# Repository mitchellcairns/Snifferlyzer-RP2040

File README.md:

# Snifferlyzer PCB
Snifferlyzer is a PCB for RP2040 facilitating the device to be used as a logic analyzer/USB Sniffer.

## Software and PCB License
<br />This firmware and PCB model are licensed under a <a rel="license" href="http://creativecommons.org/licenses/by-nc-sa/3.0/">Creative Commons Attribution-NonCommercial-ShareAlike 3.0 Unported License</a>.

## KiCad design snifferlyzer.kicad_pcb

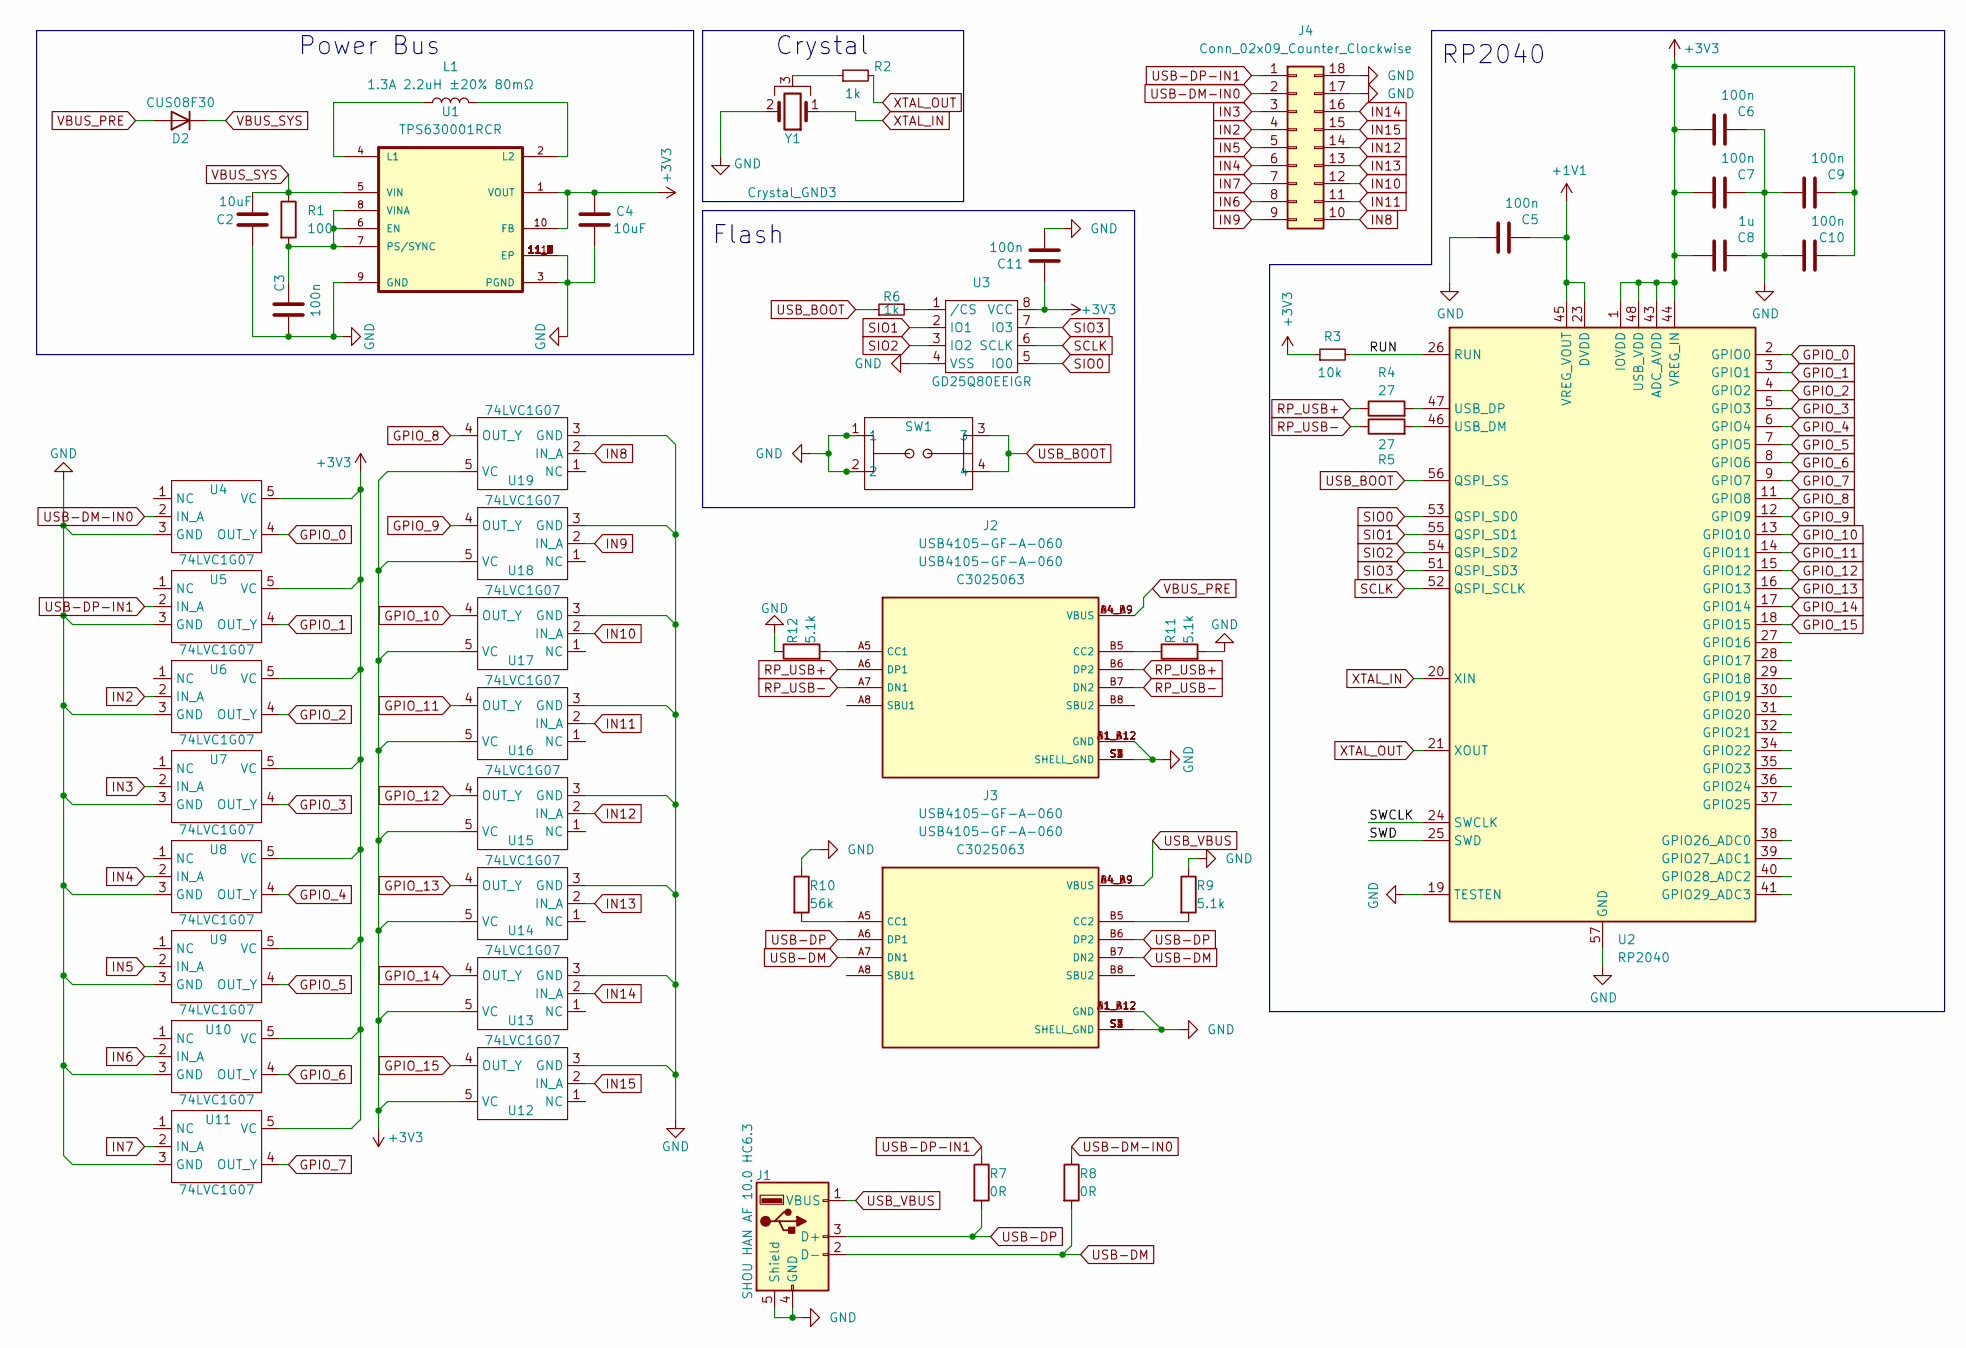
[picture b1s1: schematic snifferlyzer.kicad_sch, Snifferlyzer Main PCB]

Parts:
C2, C4: 10uF; C_0805_2012Metric
C3, C6, C11: 100n; C_0201_0603Metric
C5, C7, C9, C10: 100n; C_0402_1005Metric
C8: 1u; C_0402_1005Metric
D2: CUS08F30; D_SOD-323_HandSoldering; MPN CUS08F30
J1: SHOU HAN AF 10.0 HC6.3; AF 10.0 HC6.3; MPN AF 10.0 HC6.3; LCSC C456017
J2, J3: USB4105-GF-A-060; GCT_USB4105-GF-A-060; MPN USB4105-GF-A-060
J4: Conn_02x09_Counter_Clockwise; PinHeader_2x09_P2.54mm_Vertical; MPN X6521WV-2x09H-C60D30; LCSC C706899
L1: 1.3A 2.2uH ±20% 80mΩ; L_1008_2520Metric; MPN MIP25202R2MBE; LCSC C315721
R1: 100; R_0201_0603Metric
R2, R6: 1k; R_0201_0603Metric
R3: 10k; R_0201_0603Metric
R4, R5: 27; R_0201_0603Metric
R7, R8: 0R; R_0805_2012Metric
R9, R11, R12: 5.1k; R_0805_2012Metric
R10: 56k; R_0805_2012Metric
SW1: 1TS026A-1000-0550; MPN 1TS026A-1000-0550; LCSC C913778
U1: TPS630001RCR; VREG_V62_16624-01YE; MPN TPS63001DRCR
U2: RP2040; QFN-56-1EP_7x7mm_P0.4mm_EP3.2x3.2mm; MPN RP2040
U3: GD25Q80EEIGR; USON-8-EP(2x3); MPN GD25Q80EEIGR; LCSC C2874937
U4, U5, U6, U7, U8, U9, U10, U11, U12, U13, U14, U15, U16, U17, U18, U19: 74LVC1G07; SOT-353_SC-70-5; MPN SN74LVC1G07DCKR(UMW); LCSC C7394033
Y1: Crystal_GND3; Resonator_SMD_Murata_CSTxExxV-3Pin_3.0x1.1mm; MPN CSTNE12M0GH5L000R0

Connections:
+1V1: C5.2, U2.23 (DVDD), U2.45 (VREG_VOUT), U2.50 (DVDD)
+3V3: C4.1, C6.1, C7.1, C8.1, C9.2, C10.2, C11.1, R3.1, U1.1 (VOUT), U1.10 (FB), U2.1 (IOVDD), U2.10 (IOVDD), U2.22 (IOVDD), U2.33 (IOVDD), U2.42 (IOVDD), U2.43 (ADC_AVDD), U2.44 (VREG_IN), U2.48 (USB_VDD), U2.49 (IOVDD), U3.8 (VCC), U4.5 (VC), U5.5 (VC), U6.5 (VC), U7.5 (VC), U8.5 (VC), U9.5 (VC), U10.5 (VC), U11.5 (VC), U12.5 (VC), U13.5 (VC), U14.5 (VC), U15.5 (VC), U16.5 (VC), U17.5 (VC), U18.5 (VC), U19.5 (VC)
/RUN: R3.2, U2.26 (RUN)
/SWCLK: U2.24 (SWCLK)
/SWD: U2.25 (SWD)
GND: C2.1, C3.1, C4.2, C5.1, C6.2, C7.2, C8.2, C9.1, C10.1, C11.2, J1.4 (GND), J1.5 (Shield), J2.A1_B12 (GND), J2.B1_A12 (GND), J2.S1 (SHELL_GND), J2.S2 (SHELL_GND), J2.S3 (SHELL_GND), J2.S4 (SHELL_GND), J3.A1_B12 (GND), J3.B1_A12 (GND), J3.S1 (SHELL_GND), J3.S2 (SHELL_GND), J3.S3 (SHELL_GND), J3.S4 (SHELL_GND), J4.17, J4.18, R9.1, R10.1, R11.2, R12.1, SW1.1, SW1.2, U1.3 (PGND), U1.9 (GND), U1.11 (EP), U1.11_1 (EP), U1.11_2 (EP), U1.11_3 (EP), U1.11_4 (EP), U1.11_5 (EP), U1.11_6 (EP), U1.11_7 (EP), U1.11_8 (EP), U2.19 (TESTEN), U2.57 (GND), U3.4 (VSS), U4.3 (GND), U5.3 (GND), U6.3 (GND), U7.3 (GND), U8.3 (GND), U9.3 (GND), U10.3 (GND), U11.3 (GND), U12.3 (GND), U13.3 (GND), U14.3 (GND), U15.3 (GND), U16.3 (GND), U17.3 (GND), U18.3 (GND), U19.3 (GND), Y1.2
GPIO_0: U2.2 (GPIO0), U4.4 (OUT_Y)
GPIO_1: U2.3 (GPIO1), U5.4 (OUT_Y)
GPIO_2: U2.4 (GPIO2), U6.4 (OUT_Y)
GPIO_3: U2.5 (GPIO3), U7.4 (OUT_Y)
GPIO_4: U2.6 (GPIO4), U8.4 (OUT_Y)
GPIO_5: U2.7 (GPIO5), U9.4 (OUT_Y)
GPIO_6: U2.8 (GPIO6), U10.4 (OUT_Y)
GPIO_7: U2.9 (GPIO7), U11.4 (OUT_Y)
GPIO_8: U2.11 (GPIO8), U19.4 (OUT_Y)
GPIO_9: U2.12 (GPIO9), U18.4 (OUT_Y)
GPIO_10: U2.13 (GPIO10), U17.4 (OUT_Y)
GPIO_11: U2.14 (GPIO11), U16.4 (OUT_Y)
GPIO_12: U2.15 (GPIO12), U15.4 (OUT_Y)
GPIO_13: U2.16 (GPIO13), U14.4 (OUT_Y)
GPIO_14: U2.17 (GPIO14), U13.4 (OUT_Y)
GPIO_15: U2.18 (GPIO15), U12.4 (OUT_Y)
IN2: J4.4, U6.2 (IN_A)
IN3: J4.3, U7.2 (IN_A)
IN4: J4.6, U8.2 (IN_A)
IN5: J4.5, U9.2 (IN_A)
IN6: J4.8, U10.2 (IN_A)
IN7: J4.7, U11.2 (IN_A)
IN8: J4.10, U19.2 (IN_A)
IN9: J4.9, U18.2 (IN_A)
IN10: J4.12, U17.2 (IN_A)
IN11: J4.11, U16.2 (IN_A)
IN12: J4.14, U15.2 (IN_A)
IN13: J4.13, U14.2 (IN_A)
IN14: J4.16, U13.2 (IN_A)
IN15: J4.15, U12.2 (IN_A)
unnamed: J2.A5 (CC1), R12.2
unnamed: J2.B5 (CC2), R11.1
unnamed: J3.A5 (CC1), R10.2
unnamed: J3.B5 (CC2), R9.2
unnamed: R2.1, Y1.3
unnamed: C3.2, R1.2, U1.6 (EN), U1.7 (PS/SYNC), U1.8 (VINA)
unnamed: L1.1, U1.4 (L1)
unnamed: L1.2, U1.2 (L2)
unnamed: R5.2, U2.46 (USB_DM)
unnamed: R4.2, U2.47 (USB_DP)
unnamed: R6.2, U3.1 (/CS)
RP_USB+: J2.A6 (DP1), J2.B6 (DP2), R4.1
RP_USB-: J2.A7 (DN1), J2.B7 (DN2), R5.1
SCLK: U2.52 (QSPI_SCLK), U3.6 (SCLK)
SIO0: U2.53 (QSPI_SD0), U3.5 (IO0)
SIO1: U2.55 (QSPI_SD1), U3.2 (IO1)
SIO2: U2.54 (QSPI_SD2), U3.3 (IO2)
SIO3: U2.51 (QSPI_SD3), U3.7 (IO3)
USB-DM: J1.2 (D-), J3.A7 (DN1), J3.B7 (DN2), R8.2
USB-DM-IN0: J4.2, R8.1, U4.2 (IN_A)
USB-DP: J1.3 (D+), J3.A6 (DP1), J3.B6 (DP2), R7.2
USB-DP-IN1: J4.1, R7.1, U5.2 (IN_A)
USB_BOOT: R6.1, SW1.3, SW1.4, U2.56 (QSPI_SS)
USB_VBUS: J1.1 (VBUS), J3.A4_B9 (VBUS), J3.B4_A9 (VBUS)
VBUS_PRE: D2.2 (A), J2.A4_B9 (VBUS), J2.B4_A9 (VBUS)
VBUS_SYS: C2.2, D2.1 (K), R1.1, U1.5 (VIN)
XTAL_IN: U2.20 (XIN), Y1.1
XTAL_OUT: R2.2, U2.21 (XOUT)

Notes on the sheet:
RP2040
Flash
Crystal
Power Bus

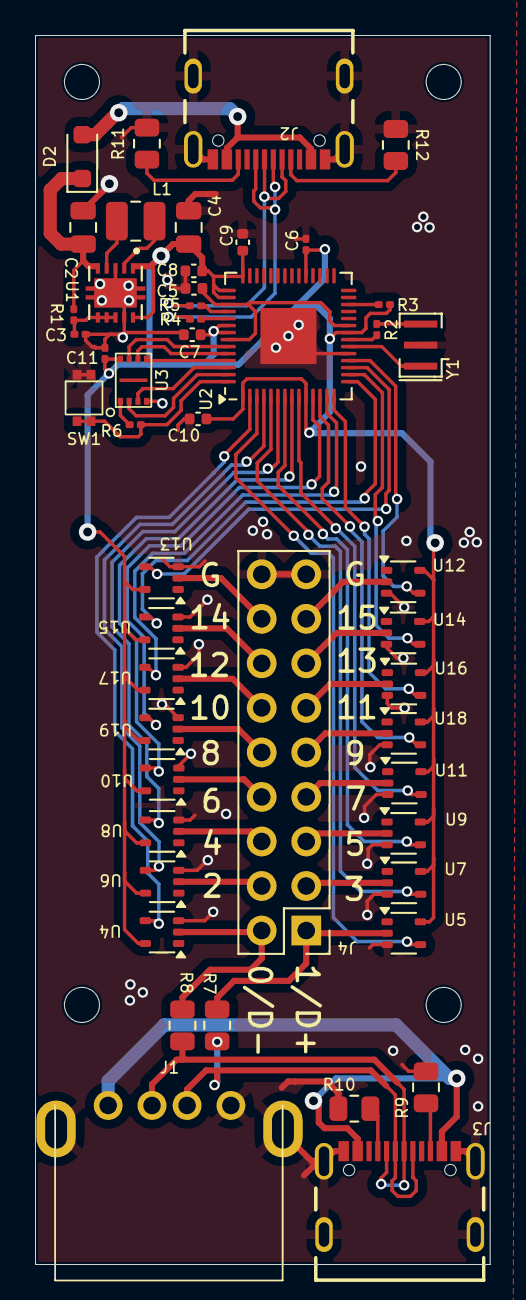
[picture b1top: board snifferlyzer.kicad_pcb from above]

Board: 2 copper layers, 25.9 x 70.1 mm, 49 parts (0 on the bottom side), 62 nets.

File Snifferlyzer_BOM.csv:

"Reference","Value","Datasheet","Footprint","Qty","DNP","LCSC","MPN"
"C2,C4","10uF","~","Capacitor_SMD:C_0805_2012Metric","2","","",""
"C3,C6,C11","100n","~","Capacitor_SMD:C_0201_0603Metric","3","","",""
"C5,C7,C9,C10","100n","~","Capacitor_SMD:C_0402_1005Metric","4","","",""
"C8","1u","~","Capacitor_SMD:C_0402_1005Metric","1","","",""
"D2","CUS08F30","","Diode_SMD:D_SOD-323_HandSoldering","1","","","CUS08F30"
"J1","SHOU HAN AF 10.0 HC6.3"," ~","snifferlyzer-lib:AF 10.0 HC6.3","1","","C456017"," AF 10.0 HC6.3"
"J2,J3","USB4105-GF-A-060","https://mm.digikey.com/Volume0/opasdata/d220001/medias/docus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","snifferlyzer-lib:GCT_USB4105-GF-A-060","2","","","USB4105-GF-A-060"
"J4","Conn_02x09_Counter_Clockwise","https://www.lcsc.com/datasheet/lcsc_datasheet_2110111530_XKB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","Connector_PinHeader_2.54mm:PinHeader_2x09_P2.54mm_Vertical","1","","C706899","X6521WV-2x09H-C60D30"
"L1","1.3A 2.2uH ±20% 80mΩ","~","Inductor_SMD:L_1008_2520Metric","1","","C315721","MIP25202R2MBE"
"R1","100","~","Resistor_SMD:R_0201_0603Metric","1","","",""
"R2,R6","1k","~","Resistor_SMD:R_0201_0603Metric","2","","",""
"R3","10k","~","Resistor_SMD:R_0201_0603Metric","1","","",""
"R4,R5","27","~","Resistor_SMD:R_0201_0603Metric","2","","",""
"R7,R8","0R","~","Resistor_SMD:R_0805_2012Metric","2","","",""
"R9,R11,R12","5.1k","~","Resistor_SMD:R_0805_2012Metric","3","","",""
"R10","56k","~","Resistor_SMD:R_0805_2012Metric","1","","",""
"SW1","1TS026A-1000-0550","https://datasheet.lcsc.com/lcsc/2201131300_HYP--Hongyuan-Pre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","hhl:1TS026A-1000-0550","1","","C913778","1TS026A-1000-0550"
"U1","TPS630001RCR","","hhl:VREG_V62_16624-01YE","1","","","TPS63001DRCR"
"U2","RP2040","${KIPRJMOD}/../progcc_v3_libs/docs/rp2040-datasheet.pdf","Package_DFN_QFN:QFN-56-1EP_7x7mm_P0.4mm_EP3.2x3.2mm","1","","","RP2040"
"U3","GD25Q80EEIGR","https://datasheet.lcsc.com/lcsc/2108150330_GigaDevice-Semico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","hhl:USON-8-EP(2x3)","1","","C2874937","GD25Q80EEIGR"
"U4,U5,U6,U7,U8,U9,U10,U11,U12,U13,U14,U15,U16,U17,U18,U19","74LVC1G07","https://www.lcsc.com/datasheet/lcsc_datasheet_2403202220_UMW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","Package_TO_SOT_SMD:SOT-353_SC-70-5","16","","C7394033","SN74LVC1G07DCKR(UMW)"
"Y1","Crystal_GND3","~","Crystal:Resonator_SMD_Murata_CSTxExxV-3Pin_3.0x1.1mm","1","","","CSTNE12M0GH5L000R0"

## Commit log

2024-05-21 Initial files commit
